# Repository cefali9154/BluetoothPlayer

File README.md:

# Bluetooth [WIP]
STM32 Bluetooth Audio Player

This repository documents my work designing, building, programming, and testing a Bluetooth audio player. Some of this log has been written retroactively, but I try to capture what my thoughts were at the time. 

## Motivation:
This project started as a request from a friend. He asked if I could make a music player that he could wear as a watch and stream to Bluetooth headphones. I had done some work before with FPGAs using SD cards so I was familiar with the protocol. I determined that this would be challenging enough to be a) fun, and b) educational, while still being possible/practical given my skills and equipment.

## Preliminary Requirements
Much of this project would be serving as a learning experience. Prior to this I only had experience with programming MIPS (PIC32) microcontrollers in class or in smaller personal projects. Additionally this work had only minor hardware integration. This would be my first project to combine significant hardware design and development (component selection, schematic design, PCB layout, board assembly, board testing) with full programming. Over time I had accumulated drivers/libraries for PIC devices but I had not worked with ARM devices yet. I should explain that I determined early on to use an STM32 processor due to the prevalence in industry.

Because this would serve as a learning experience, I did not have a firm idea of what I would be capable of for this. This led to establishing loose requirements so that way based on what I learned, I could adjust the design.

My preliminary requirements were (in no significant order):

1. Read an audio file off of a micro SD card and stream the file over Bluetooth to a speaker or headphones
1. The whole module should be able to be worn (with a 3D-printed housing or other mount) on the wrist as a watch-sized device
1. Be battery powered and have a streaming battery life of >90 minutes
1. Be able to recharge the battery via a micro USB port
1. Allow the user to:
    1. Pause/Play
    1. Increase/Decrease the volume
    1. Skip to the Next/Previous song
    1. Allow the user to choose between a "shuffle" function and sequential playback
1. Use an STM32 processor
1. Keep the total cost <$75 USD

## Component Selection
Component selection was centered on the Bluetooth radio/module and the host microcontroller. The radio selected was the SierraWireless BC127. The selection was driven by the following major factors (note that cost and size factor into all components):
1. Embedded Bluetooth Stack
1. Low (15mA) streaming current consumption
1. Ability to be powered directly from a lithium battery and integrated charging circuit 
1. Availability of Sparkfun Arduino libraries. 

I had planned to leverage the Arduino libraries to help with the programming, but it has proven easier and quicker to write my own functions rather than port the Arduino ones.

The BC127 supports the I2S protocol for digital audio and is controlled via UART. This then led to the selection criteria for the host microcontroller. The selected microcontroller was a STM32L051C8 in a 48-pin LQFP package. The major factors in this decision were:
1. Included peripherals
    1. I2S for digital audio transfer to BC127
    1. SPI for SD card communication
    1. 2x UART for communication between STM32 and BC127 and communication between SM32 and a PC for debugging and configuration
1. EEPROM for user setting storage
1. DMA for SD (SPI) reception and I2S transmission
1. Up to 32MHz clock 
1. Sufficient RAM for data buffers
1. Low current consumption
1. 48-pin LQFP is easily hand-soldered

With these two core components selected, the remaining components were chosen during the circuit design process based off of either reference circuits from the datasheets, or general design knowledge.

## Circuit Design
Schematic design and PCB layout was done in EagleCAD. The design used many common components that already had component models, but several libraries and models had to be made still. 

Testing of some circuit aspects (e.g. the power on/off circuit) were modeled in OrCad and simulated in PSPICE as a sanity check.

The design of the battery charging circuit is based off of the Application Note for the BC127. In more recent versions of the Application Note it is made clear that the charging circuit shown bypasses the internal regulator and uses an external fast charge. Had I understood this at the time then some space could have been saved on the PCB. 

### Schematic

The finalized schematic:

STM32CoreMX was used to simplify STM32 pin selections during the schematic design.

### PCB

The finalized PCB layout:

The layout is not ideal as there are some larger loops, and my high frequency lines do alternate between layers, but when doing the layout I determined that this would likely not be an issue. This is because the majority of the traces are DC signals and the highest frequency lines are my I2S clock and SD SPI clock lines. The I2S clock runs at about 3 MHz and the SPI clock runs at about 4 MHz. 

1206 size resistors and capacitors were used for the ease of soldering. In hindsight I could have at least gone down to 0805 size and hand soldered them easily. This would have saved space as well.

A 2-layer PCB was used in order to save cost, but a 4-layer board may have resulted in a more compact design. However, this would have still been limited by the size of the battery, micro SD card slot, and buttons for control.

### Assembly and Hardware Testing

The unassembled PCB:
PCB Top | PCB Bottom
--------|-----------
 | 

At the time of assembly, the only lab equipment I had was a soldering iron with various tips, a set of "Helping Hands", a magnifying glass, a handheld multimeter, and flux, solder, wire, etc. (Since then I have upgraded my home lab to have a proper work area along with a 5-20x stereo microscope, 4-channel 100MHz oscilloscope, variable power supply, various fine tools etc.)

The assembled PCB:
PCB Top | PCB Bottom
--------|-----------
 | 

Given the tools available at the time I am satisfied with the quality of the assembled PCB.

Testing was done in various stages of PCB assembly. Once the USB port and 3.3V regulator were installed, the board was powered and the voltage was checked to verify 3.3V. Once this tested satisfactory then the remaining components were installed with continuity checks and voltage checks along the way to verify operation. 

A set of pads for use with the ST-Link programmer and a set of pads for UART communication with a PC were then used to begin programming.

## Programming
A significant drawback to the requirement to keep the total cost under $75 was that no development boards or discovery kits were used. This meant that programming could not begin in any significant way until the PCB design was finalized, assembled, and tested. 

As stated earlier, STM32CubeMX was used to assist with pin selection. This also allowed for easy configuration of the clock and peripherals and generation of the initial code. 

As programming began, an effort was made to utilize the HAL drivers as much as possible, however in many cases (especially early on in the program) it was easier or faster (from a code execution perspective) to interact with the registers directly. This had the added benefit of giving me a much better understanding of the environment versus if I only used the HAL drivers.

Data is stored on the SD card. It is read via SPI1 using DMA in order to reduce processor load. FatFs is used to handle the file reads. Data is read into a buffer with an upper and a lower half. This data is then sent over I2S using DMA to the BC127. The upper half of the buffer is filled while the lower half is being sent and vice versa. 

The BC127 is controlled via UART. The STM32 send and receives commands or notifications over UART2. In order to support configuration and debugging, this UART2 is mirrored to UART1. UART1 interfaces with a PC for terminal (PuTTY) display and control.

The buttons on the PCB are sampled and then used for control of the device. (Volume up/down, pause/play etc.)

The program was written in phases with testing at every point of development. An outline of the phases and issues/points of note are shown below:

1. Configuring UART1 for connection to PC. printf() was redefined to output over UART for easier use.
1. Implementation of hardware I/O layer for FatFs. Much of this information and code was taken from examples provided in the "Mastering STM32" book by Carmine Noviello. DMA was configured. SD card read tests passed.
1. Implementation of UART2 for communication with the BC127. Also set up as a pass-through for UART1 so the BC127 could be configured from a PC directly. Battery charging enabled using the BC127 because the BC127 will not function without a battery.
1. Debouncing and Oneshot was added and tested for user inputs.
1. Audio streaming was established. Audio data was read in with DMA but audio streaming was set up with I2S interrupts. I did not fully understand the HAL_DMA drivers so in the interest of progress, interrupts were used. The audio in the wav file is little endian, but the transmission is big endian so the bytes had to be switched. Volume control was implemented by shifting the bits of the audio samples to the right. At this point, I only had one Bluetooth Speaker to test with. The audio on this would crackle when playing off of this, but when connected to another device (e.g. a phone), the audio would be clear. I figured this was a timing issue with the audio transmission or a clock jitter issue but had no way to verify yet. Several months passed before work restarted.
1. Work restarted once I acquired an oscilloscope. I was able to see that there was a periodic dropout in the transmission. I optimized the code and reconfigured the interrupt priorities. The transmission dropout disappeared but the audio was still crackling. Around this time I also recieved a different Bluetooth speaker. When tested with this, I got good quality audio except for a drop that happens every 10 seconds. I provide more information about this in the "Current Issues" section.
1. DMA was successfully configured for I2S transmission. It was not entirely clear how to implement it with a circular buffer from the HAL manual, but trial and error along with significant googling provided an answer.
1. Major refactoring of almost all of the code. To this point, this had been more of a test platform with poor coding practices. I rewrote most of it with good practices that were learned from reading through example code and high-profile open source projects to see how code is arranged in them.
1. Implementation of a state machine to handle user inputs, BC127 configuration, pairing of new devices, and file navigation.
1. Implement error handling and the ability to accept multiple WAV configurations (e.g. mono or stereo). [Current Step]
1. Implement LED controller to visually show important information about the device (battery status, connection status etc).
1. Perform a final optimization of the code and decrease the clock speed as much as possible to increase battery life.

## Current Issues
1. Every 10 seconds, the Bluetooth stream goes silent for a moment and then comes back. After observing the I2S signal, there is no issue with that, so there must be something going on with the actual Bluetooth connection between the BC127 and the speaker. My current theory is that the BC127 will only connect with the SBC codec when it is acting as a source. When I connect my phone to the speakers, it uses the AAC codec. I believe that the periodic drop is due to the speaker not being able to handle the SBC bitrate. This issue occurs with both mono and stereo files I have contacted SierraWireless support regarding this but they have not been able to explain. Another issue I have is that when I configure the BC127 to use 44.1 KHz audio, it still connects to the speaker at 48 KHz. I have found posts from others online with this same issue but so far no one has had any answers. If I configure the BC127 to use 44.1 KHz audio, it will still connect at 48 KHz, but the audio will not cut out every 10 seconds. This is not a viable option though because the audio will be slowed down and there are frequent pops and crackles.
1. The BC127 datasheet shows the voltage range as 3.3 - 4.2 VDC. However, when the battery voltage drops below ~3.8 VDC, the device will initially have difficulty connecting or maintaining a Bluetooth link, and as the voltage drops further, the device may enter a perpetual reboot cycle. Initially I thought that for some reason there was a voltage drop across the power on circuit and while the battery may be 3.8 VDC, the actual voltage in was less. I observed the voltage with the oscilloscope and saw that this was not the case. My next step in debugging this will be to bypass the external charging transistor (BCX51T1). This was implemented based off of what was at the time, the current application note for the BC127. In more recent versions of the application note, this transistor is not present. It is made clear that this transistor is for external charging, and to not include it if you are only using the internal charging circuit. 

## Lessons Learned
1. The BC127 module has proven difficult to work with. I believe this can be attributed to the small user base and sometimes unclear documentation.
1. A development board is a valuable investment and would save significant time in future projects.
1. The HAL drivers are useful, but do not get too hung up on using them. Direct register access can be quicker and easier.
1. If a new section of code is written and tested, clean it up before moving on (or write it properly in the first place, but when trying new things this can take too much time), or else the code ends up being messy later.
1. In general I have gained a much better understanding of the operation of the microcontroller and organization and design of code.

## Future Work Ideas
1. Redo the PCB layout with a 4-layer PCB. This should allow for size reduction and proper signal routing.
1. Implement a discrete MP3 codec to decode MP3's. By allowing the use of MP3s, the file size would be significantly smaller. MP3s are also more common for music libraries.
1. Allow the user to access the SD card via the micro USB port, which is currently only used for charging.

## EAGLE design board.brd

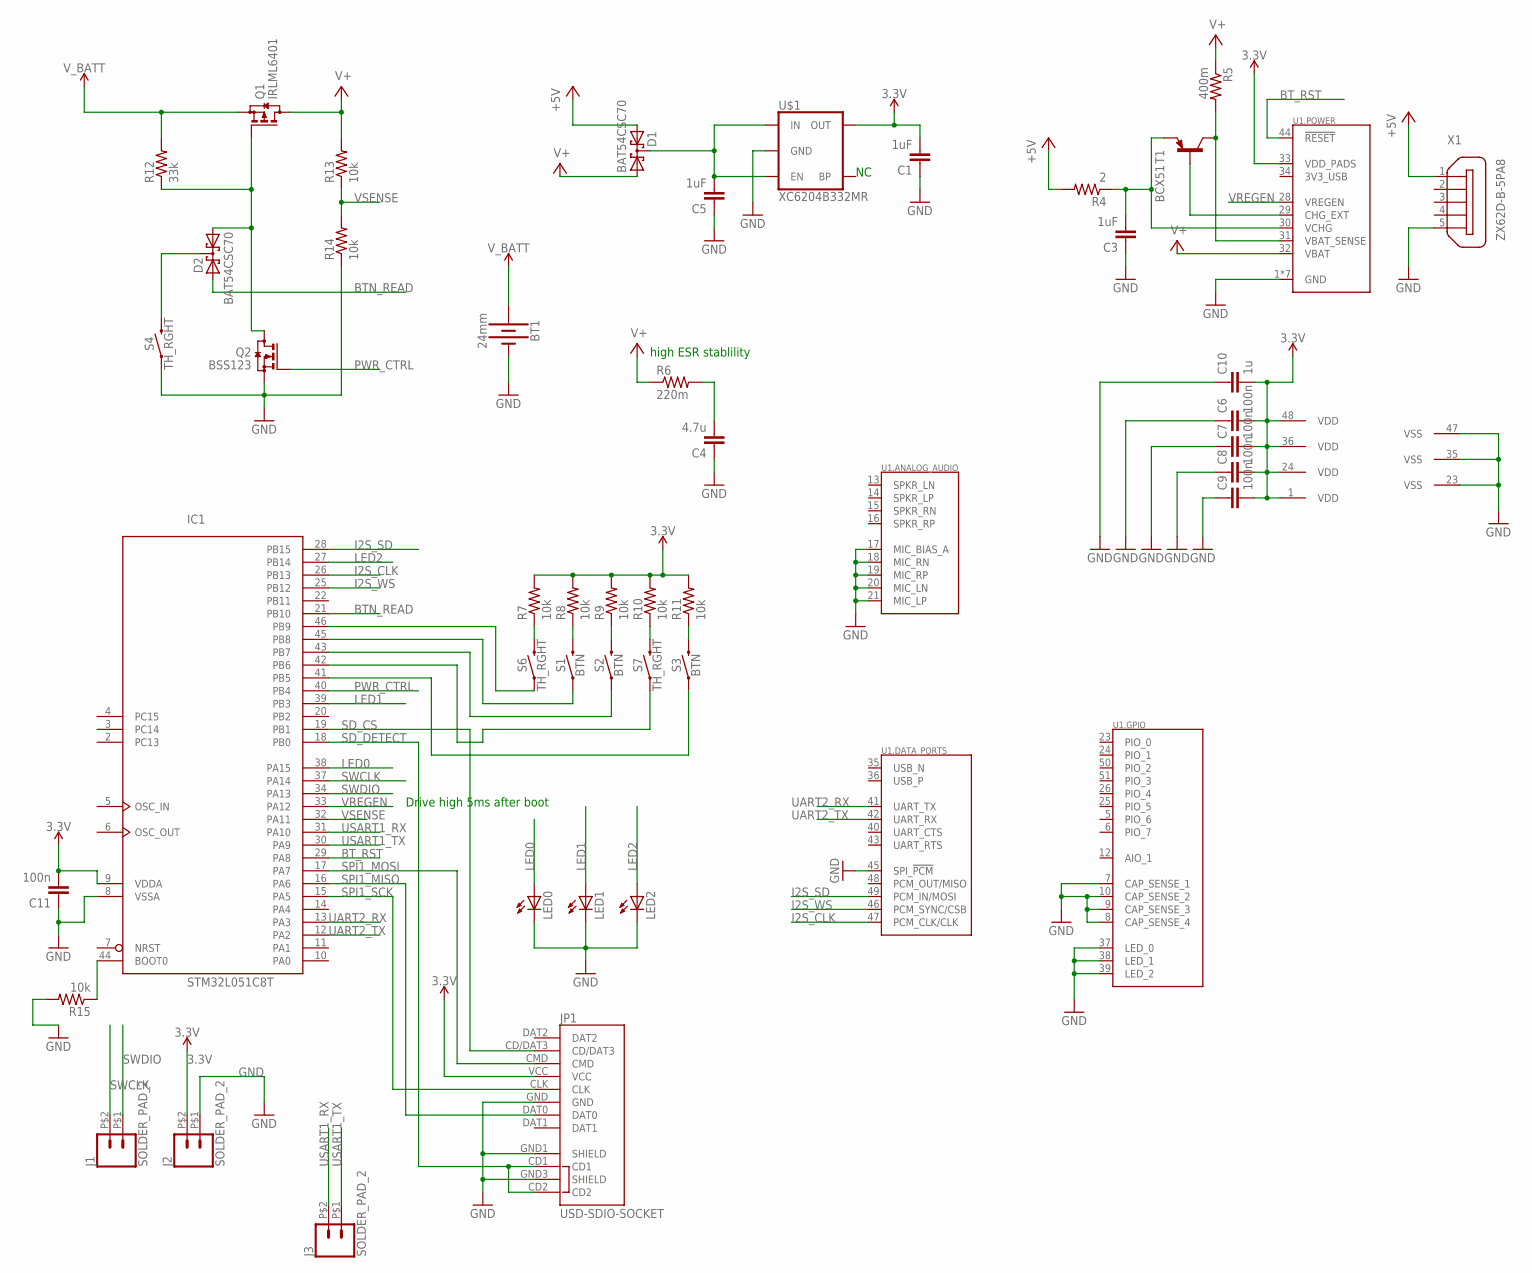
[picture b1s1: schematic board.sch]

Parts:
BT1: 24mm; BATTCON_24.5MM_PTH
C1, C3, C5: 1uF; C1206
C4: 4.7u; C1206
C6, C7, C8, C9, C11: 100n; C0805
C10: 1u; C0805
D1, D2: BAT54CSC70; SOT323-R
IC1: STM32L051C8T; LQFP48
J1, J2, J3: SOLDER_PAD_2
JP1: USD-SDIO-SOCKET; MICRO-SD-SOCKET-SDIO
LED0, LED1, LED2: LEDSML0805; SML0805
Q1: IRLML6401; SOT23
Q2: BSS123; SOT23
R4: 2; M1206
R5: 400m; M1206
R6: 220m; M1206
R7, R8, R9, R10, R11, R13, R14, R15: 10k; R0805
R12: 33k; R0805
S1, S2, S3: BTN; TACTILE_SWITCH_SMD_6.2MM_TALL
S4, S6, S7: TH_RGHT; TACTILE_SWITCH_PTH_RIGHT_ANGLE
T1: BCX51; SOT89-ECB
U1: BC127"; BC127
U$1: XC6204B332MR; SOT23-5
X1: ZX62D-B-5PA8

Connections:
3.3V: C1.2, C6.2, C7.2, C8.2, C9.2, C10.2, C11.2, IC1.1 (VDD), IC1.9 (VDDA), IC1.24 (VDD), IC1.36 (VDD), IC1.48 (VDD), J2.P$2 (2), JP1.VCC, R7.2, R8.2, R9.2, R10.2, R11.2, U1.33 (VDD_PADS), U$1.5 (OUT)
+5V: D1.2 (A2), R4.2, X1.1
BOOT0: IC1.44 (BOOT0), R15.1
BTN_READ: D2.2 (A2), IC1.21 (PB10)
BT_RST: IC1.29 (PA8), U1.44 (!RESET)
GND: BT1.2 (-), C1.1, C3.1, C4.1, C5.1, C6.1, C7.1, C8.1, C9.1, C10.1, C11.1, IC1.8 (VSSA), IC1.23 (VSS), IC1.35 (VSS), IC1.47 (VSS), J2.P$1 (1), JP1.GND, JP1.GND1 (SHIELD), JP1.GND3 (SHIELD), LED0.C, LED1.C, LED2.C, Q2.2 (S), R14.1, R15.2, S4.1, U1.1 (GND), U1.2 (GND), U1.3 (GND), U1.4 (GND), U1.7 (CAP_SENSE_1), U1.8 (CAP_SENSE_4), U1.9 (CAP_SENSE_3), U1.10 (CAP_SENSE_2), U1.11 (GND), U1.17 (MIC_BIAS_A), U1.18 (MIC_RN), U1.19 (MIC_RP), U1.20 (MIC_LN), U1.21 (MIC_LP), U1.22 (GND), U1.27 (GND), U1.37 (LED_0), U1.38 (LED_1), U1.39 (LED_2), U1.45 (SPI_!PCM), U$1.2 (GND), X1.5
I2S_CLK: IC1.26 (PB13), U1.47 (PCM_CLK/CLK)
I2S_SD: IC1.28 (PB15), U1.49 (PCM_IN/MOSI)
I2S_WS: IC1.25 (PB12), U1.46 (PCM_SYNC/CSB)
LED0: IC1.38 (PA15), LED0.A
LED1: IC1.39 (PB3), LED1.A
LED2: IC1.27 (PB14), LED2.A
unnamed: D2.1 (A1), Q1.1 (G), Q2.3 (D), R12.1
unnamed: C3.2, R4.1, T1.E, U1.30 (VCHG)
unnamed: T1.B, U1.29 (CHG_EXT)
unnamed: R5.2, T1.C, U1.31 (VBAT_SENSE)
unnamed: C4.2, R6.2
unnamed: C5.2, D1.3 (CC), U$1.1 (IN), U$1.3 (EN)
unnamed: R7.1, S6.2
unnamed: R8.1, S1.B2 (2)
unnamed: R9.1, S2.B2 (2)
unnamed: R10.1, S7.2
unnamed: R11.1, S3.B2 (2)
unnamed: IC1.46 (PB9), S6.1
unnamed: IC1.45 (PB8), S1.A2 (1)
unnamed: IC1.43 (PB7), S2.A2 (1)
unnamed: IC1.42 (PB6), S7.1
unnamed: IC1.41 (PB5), S3.A2 (1)
unnamed: D2.3 (CC), S4.2
PWR_CTRL: IC1.40 (PB4), Q2.1 (G)
SD_CS: IC1.19 (PB1), JP1.CD/DAT3
SD_DETECT: IC1.18 (PB0), JP1.CD1, JP1.CD2
SPI1_MISO: IC1.16 (PA6), JP1.DAT0
SPI1_MOSI: IC1.17 (PA7), JP1.CMD
SPI1_SCK: IC1.15 (PA5), JP1.CLK
SWCLK: IC1.37 (PA14), J1.P$2 (2)
SWDIO: IC1.34 (PA13), J1.P$1 (1)
UART2_RX: IC1.13 (PA3), U1.41 (UART_TX)
UART2_TX: IC1.12 (PA2), U1.42 (UART_RX)
USART1_RX: IC1.31 (PA10), J3.P$2 (2)
USART1_TX: IC1.30 (PA9), J3.P$1 (1)
V+: D1.1 (A1), Q1.3 (D), R5.1, R6.1, R13.2, U1.32 (VBAT)
VREGEN: IC1.33 (PA12), U1.28 (VREGEN)
VSENSE: IC1.32 (PA11), R13.1, R14.2
V_BATT: BT1.3 (+), Q1.2 (S), R12.2

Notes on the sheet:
high ESR stablility
Drive high 5ms after boot

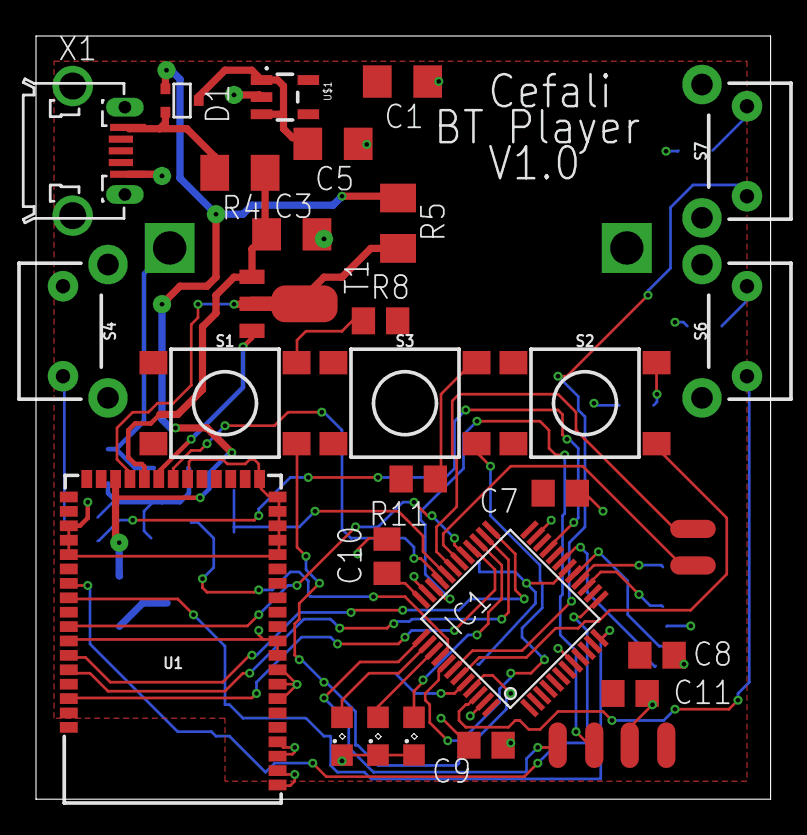
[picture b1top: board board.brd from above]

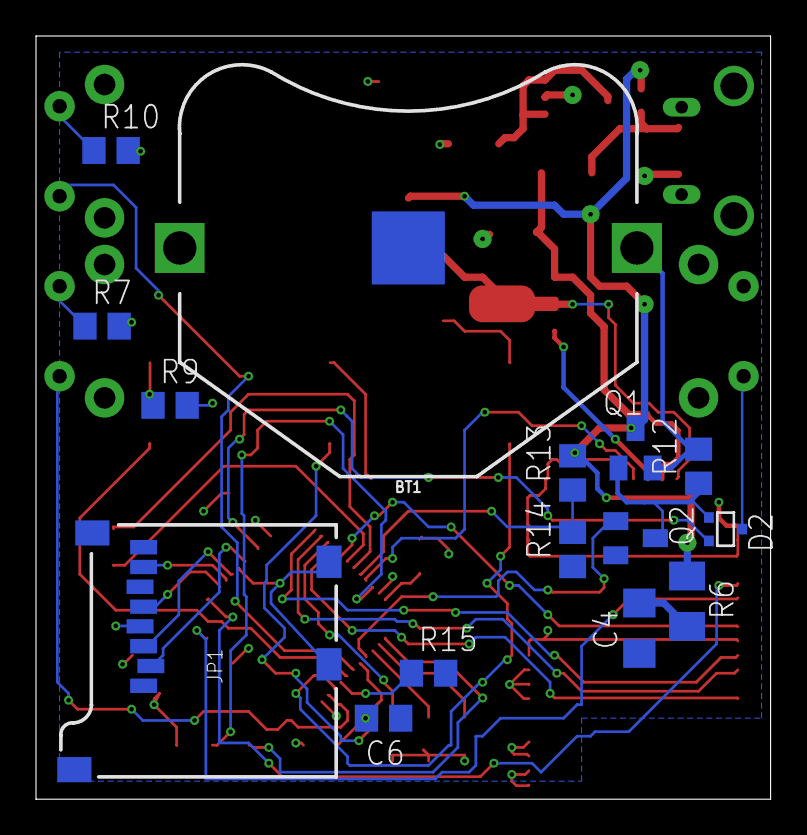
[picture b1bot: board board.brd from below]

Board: 2 copper layers, 40.8 x 42.4 mm, 45 parts (15 on the bottom side), 45 nets.

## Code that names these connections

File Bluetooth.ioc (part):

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Mcu.Name=STM32L051C(6-8)Tx
Mcu.Package=LQFP48
Mcu.UserName=STM32L051C8Tx
PA10.Mode=Asynchronous
PA10.Signal=USART1_RX
PA11.GPIOParameters=GPIO_Label
PA11.GPIO_Label=VSENSE
PA11.Signal=GPIO_Analog
PA12.GPIOParameters=GPIO_Label
PA12.GPIO_Label=VREGEN
PA12.Signal=GPIO_Output
PA13.Mode=Serial_Wire
PA13.Signal=SYS_SWDIO
PA14.Mode=Serial_Wire
PA14.Signal=SYS_SWCLK
PA15.Signal=S_TIM2_CH1
PA2.Mode=Asynchronous
PA2.Signal=USART2_TX
PA3.Mode=Asynchronous
PA3.Signal=USART2_RX
PA5.Mode=Full_Duplex_Master
PA5.Signal=SPI1_SCK
PA6.Mode=Full_Duplex_Master
PA6.Signal=SPI1_MISO
PA7.Mode=Full_Duplex_Master
PA7.Signal=SPI1_MOSI
PA8.GPIOParameters=GPIO_Label
PA8.GPIO_Label=BT_RST
PA8.Signal=GPIO_Output
PA9.Mode=Asynchronous
PA9.Signal=USART1_TX
PB0.GPIOParameters=GPIO_PuPd,GPIO_Label
PB0.GPIO_Label=SD_Detect
PB0.GPIO_PuPd=GPIO_PULLUP
PB0.Signal=GPIO_Input
PB1.GPIOParameters=PinState,GPIO_Label
PB1.GPIO_Label=SD_CS
PB1.PinState=GPIO_PIN_RESET
PB1.Signal=GPIO_Output
PB10.GPIOParameters=GPIO_PuPd,GPIO_Label
PB10.GPIO_Label=BTN_READ
PB10.GPIO_PuPd=GPIO_PULLUP
PB10.Signal=GPIO_Input
PB12.Mode=Half_Duplex_Slave
PB12.Signal=I2S2_WS
PB13.Mode=Half_Duplex_Slave
PB13.Signal=I2S2_CK
PB14.GPIOParameters=GPIO_Label
PB14.GPIO_Label=LED2
PB14.Signal=GPIO_Analog
PB15.Mode=Half_Duplex_Slave
PB15.Signal=I2S2_SD
PB3.Signal=S_TIM2_CH2
PB4.GPIOParameters=GPIO_Label
PB4.GPIO_Label=PWR_CTRL
PB4.Signal=GPIO_Output
PB5.GPIOParameters=GPIO_PuPd,GPIO_Label
PB5.GPIO_Label=S3
PB5.GPIO_PuPd=GPIO_PULLDOWN
PB5.Signal=GPIO_Input
PB6.GPIOParameters=GPIO_PuPd,GPIO_Label
PB6.GPIO_Label=S7
PB6.GPIO_PuPd=GPIO_PULLDOWN
PB6.Signal=GPIO_Input
PB7.GPIOParameters=GPIO_PuPd,GPIO_Label
PB7.GPIO_Label=S2
PB7.GPIO_PuPd=GPIO_PULLDOWN
PB7.Signal=GPIO_Input
PB8.GPIOParameters=GPIO_PuPd,GPIO_Label
PB8.GPIO_Label=S1
PB8.GPIO_PuPd=GPIO_PULLDOWN
PB8.Signal=GPIO_Input
PB9.GPIOParameters=GPIO_PuPd,GPIO_Label
PB9.GPIO_Label=S6
PB9.GPIO_PuPd=GPIO_PULLDOWN
PB9.Signal=GPIO_Input
RCC.HSE_VALUE=8000000
RCC.SYSCLKFreq_VALUE=8000000
RCC.SYSCLKSource=RCC_SYSCLKSOURCE_PLLCLK
board=custom

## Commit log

2020-06-02 Initial Commit for Online Use
2020-06-02 Organized Files
2020-06-02 Moved image files
2020-06-02 Fixed nextSong
2020-06-03 Modifications to State Machine Device now keeps the stream open when changing songs or when EOF is reached
2020-06-05 Cleaned up streamAudio and added covertToMono
2020-06-06 Modified to support stereo and mono files
    Made small fixes to state machine as well
2020-06-24 Began implementation of LED functions

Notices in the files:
parts and their libraries:
SparkFun-RF: Licensing: Creative Commons ShareAlike 4.0 International - https://creativecommons.org/licenses/by-sa/4.0
